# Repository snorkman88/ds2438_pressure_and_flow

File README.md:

# ds2438_pressure_and_flow
DS 2438 water pressure and flow sensor board

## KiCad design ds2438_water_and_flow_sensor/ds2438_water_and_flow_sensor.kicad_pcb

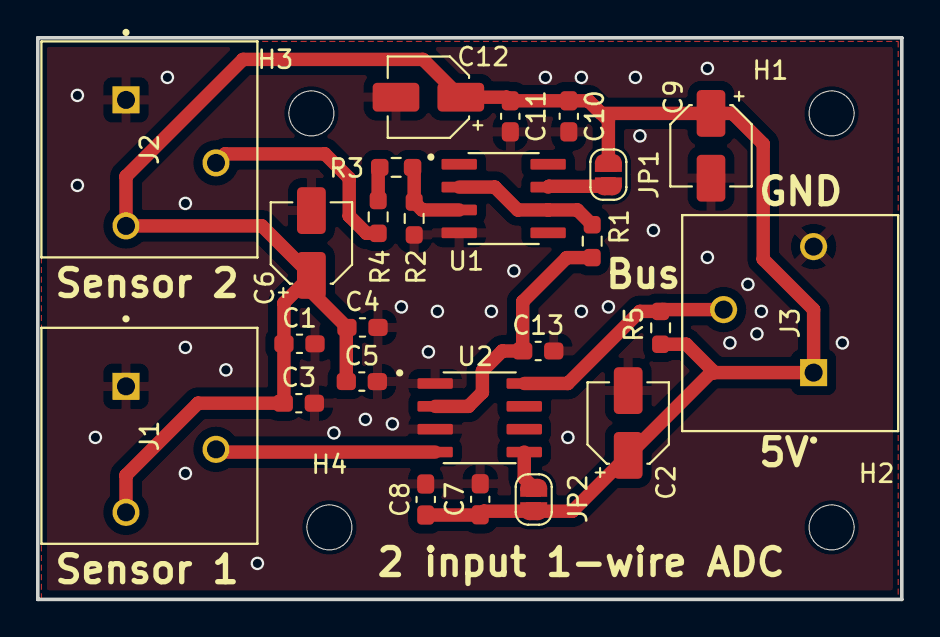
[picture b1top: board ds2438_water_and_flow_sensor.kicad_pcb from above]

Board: 2 copper layers, 48.0 x 31.2 mm, 29 parts (0 on the bottom side), 11 nets.

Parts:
C1, C3, C4, C5, C7, C8, C10, C11, C13: 0.1u; C_0603_1608Metric_Pad1.08x0.95mm_HandSolder
C2, C6, C9, C12: 10uF; CP_Elec_4x5.8
H1, H2, H3, H4: MountingHole; MountingHole_2.5mm
J1: Sensor 1; TE_1985205
J2, J3: Sensor 2; TE_1985205
JP1, JP2: SolderJumper_2_Open; SolderJumper-2_P1.3mm_Open_RoundedPad1.0x1.5mm
R1: 0; R_0603_1608Metric_Pad0.98x0.95mm_HandSolder
R2, R3: 10k; R_0603_1608Metric_Pad0.98x0.95mm_HandSolder
R4: 180k; R_0603_1608Metric_Pad0.98x0.95mm_HandSolder
R5: 4.7k; R_0603_1608Metric_Pad0.98x0.95mm_HandSolder
U1: OPA335AID; SOIC127P599X175-8N
U2: DS2438AZ_; SOIC127P600X175-8N

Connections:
/1W_Bus: J3.2, R5.2, U2.8 (DQ)
/5V_sensor_1_input: J1.2, U2.4 (VAD)
/5V_sensor_2_input: J2.2, R4.1
/250mV_sensor_2_input: C13.1, R1.2, U2.2 (VSENS+)
/VDD_Opamp: JP1.1 (A), U1.7 (V+)
GND: C1.2, C2.2, C3.2, C4.2, C5.2, C6.2, C7.2, C8.2, C9.2, C10.2, C11.2, C12.2, C13.2, J1.1, J2.1, J3.3, R2.2, U1.4 (V-), U2.1 (GND), U2.3 (VSENS-)
unnamed: JP2.1 (A), U2.5 (VDD)
unnamed: R3.1, R4.2
unnamed: R2.1, R3.2, U1.3 (+IN)
unnamed: R1.1, U1.2 (-IN), U1.6 (OUT)
VDD: C1.1, C2.1, C3.1, C4.1, C5.1, C6.1, C7.1, C8.1, C9.1, C10.1, C11.1, C12.1, J1.3, J2.3, J3.1, JP1.2 (B), JP2.2 (B), R5.1
